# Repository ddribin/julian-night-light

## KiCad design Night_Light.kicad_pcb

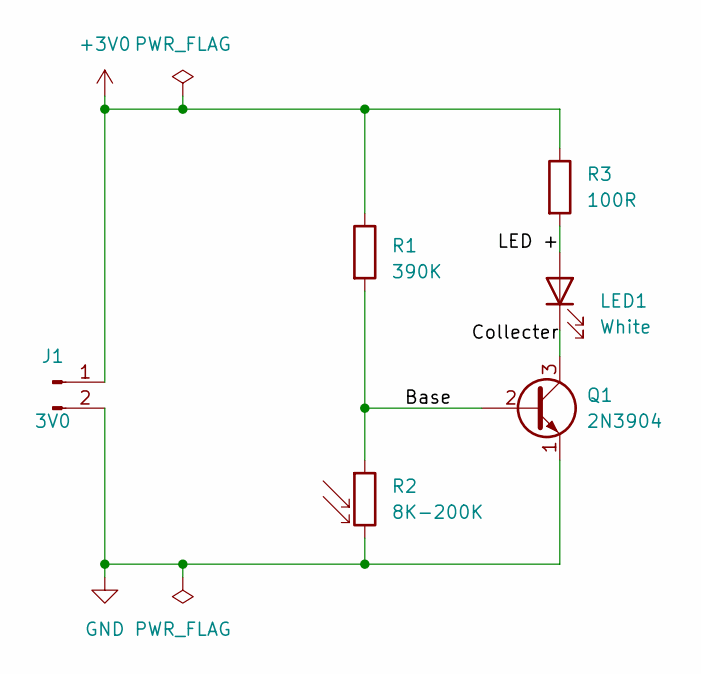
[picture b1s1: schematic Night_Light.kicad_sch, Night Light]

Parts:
J1: 3V0; SolderWire-1.5sqmm_1x02_P6mm_D1.7mm_OD3mm
LED1: White; LED_D5.0mm_Clear
Q1: 2N3904; TO-92_Inline_Wide
R1: 390K; R_Axial_DIN0207_L6.3mm_D2.5mm_P10.16mm_Horizontal
R2: 8K-200K; R_LDR_7x6mm_P5.1mm_Vertical
R3: 100R; R_Axial_DIN0207_L6.3mm_D2.5mm_P10.16mm_Horizontal

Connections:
+3V0: J1.1, R1.1, R3.1
/Base: Q1.2 (B), R1.2, R2.1
/Collecter: LED1.1 (K), Q1.3 (C)
/LED +: LED1.2 (A), R3.2
GND: J1.2, Q1.1 (E), R2.2

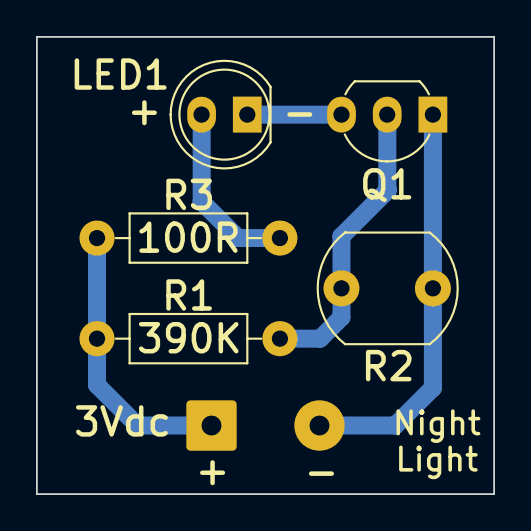
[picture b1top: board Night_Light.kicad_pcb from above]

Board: 2 copper layers, 25.4 x 25.4 mm, 6 parts (0 on the bottom side), 5 nets.

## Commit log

2023-01-05 Finished schematic
2023-01-05 Switched battery for connector, add labels, add power flags
2023-01-06 Assign all footprints
2023-01-06 Initial board layout. No traces.
2023-01-16 Finished wiring the PCB
2023-01-29 Remove mounting holes. Reduce size to 1.0x1.0. Changed some footprints to match real board.
2023-02-04 Changed size of pads
2023-02-04 Updated silkscreen and version
2023-02-15 Add mark and name
2023-02-15 Finalize mark location
2023-02-15 Finalize version and document info
2023-04-15 Upgrade to version 7 of KiCad
2023-04-15 Remove ground plane. Fixes #6
2023-04-15 Update schematic for KiCad version 7
2023-04-15 Update PCB for new KiCad 7 libraries
2023-04-15 Changed all track widths to 1mm. Fixes issue #5.
2023-04-15 Change hole sizes for resistors, photoresistor, and transistor. Fixes #2.
2023-04-15 Make power holes smaller. Fixes #3
2023-04-16 Make most of the pads a bit bigger. Fixes #1
2023-04-16 Update silkscreen. Fixes #7, #8, #9, and #11
    - Change "D1" label to "LED1". #7
    - Make silkscreen text bigger and thicker. #8
    - Add "+" and "-" to power pads. #9
    - Add LED polarity to silkscreen. #11
2023-04-22 Change R3 and add resistor values to silkscreen
2023-04-22 Copy all updated footprints into a project footprint library, to avoid DRC warnings
2023-04-22 Add .mailmap file
2023-04-22 Remove .mailmap
2023-04-22 Update settings for creating Gerber
2023-04-22 Updated back silkscreen
2023-04-22 Fix the silkscreen sizes
2023-04-22 Fix more of the top silkscreen
2023-04-22 Updated date
2023-08-03 Moved components away from edge
2023-08-03 Updated version to 1.1.1 and updated date
2023-08-04 Update output directory for schematic
2025-02-01 Update files to KiCad 8
